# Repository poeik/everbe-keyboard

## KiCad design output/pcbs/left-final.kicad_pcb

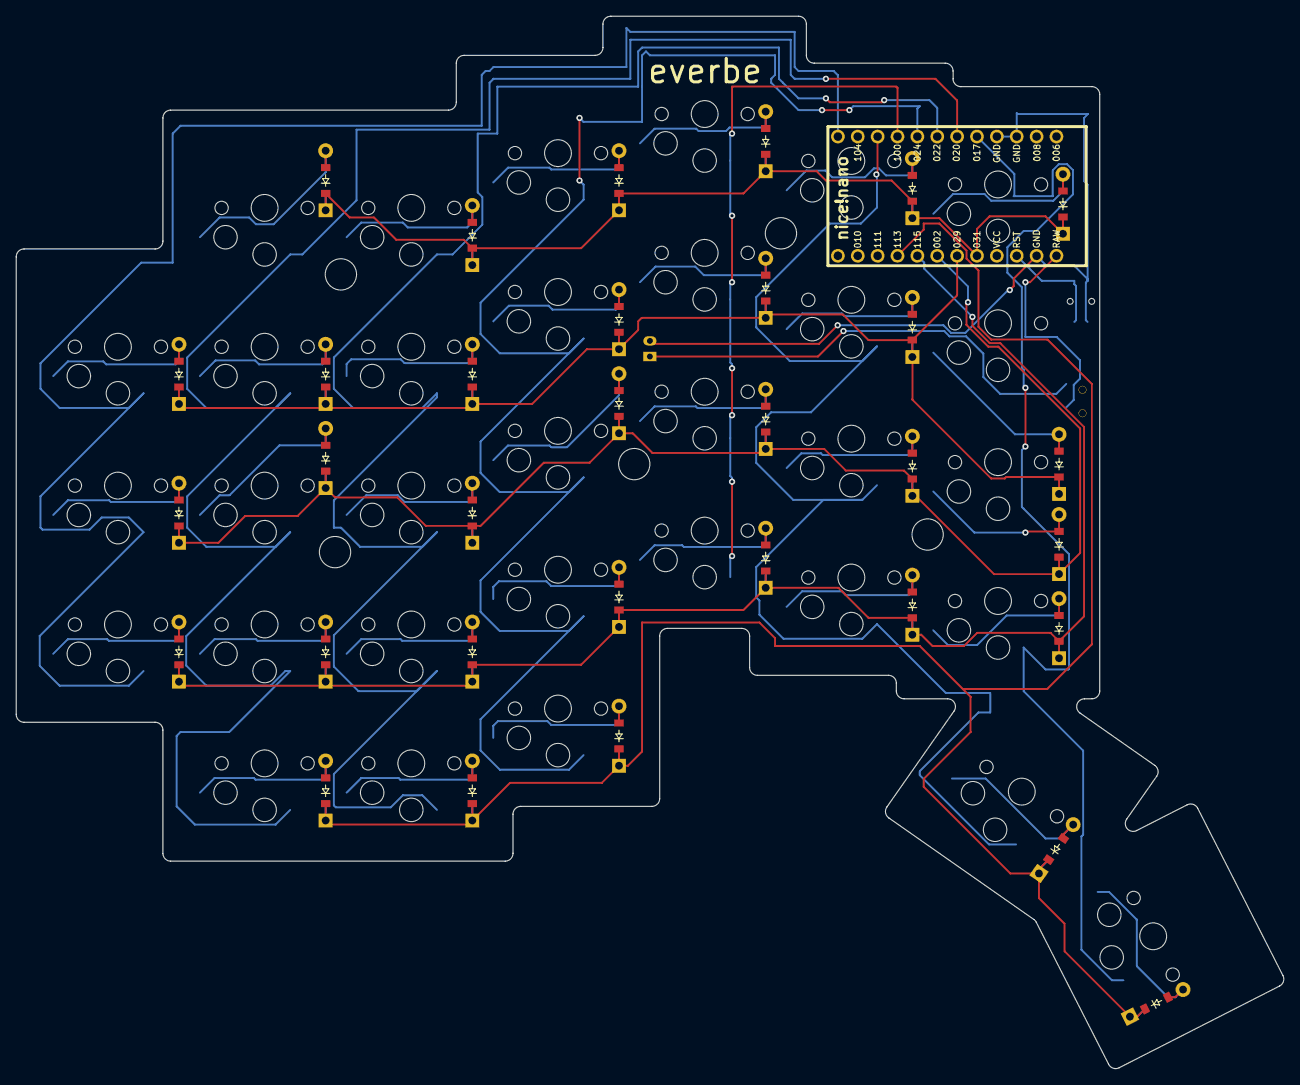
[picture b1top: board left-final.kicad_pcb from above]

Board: 2 copper layers, 162.0 x 134.5 mm, 68 parts (0 on the bottom side), 48 nets.

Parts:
B1: Panasonic_EVQPUL_EVQPUC
D1, D2, D3, D4, D5, D6, D7, D8, D9, D10, D11, D12, D13, D14, D15, D16, D17, D18, D19, D20, D21, D22, D23, D24, D25, D26, D27, D28, D29, D30, D31, D32: ComboDiode
JST1: JST_PH_S2B-PH-K_02x2.00mm_Angled
MCU1: nice_nano
S1, S2, S3, S4, S5, S6, S7, S8, S9, S10, S11, S12, S13, S14, S15, S16, S17, S18, S19, S20, S21, S22, S23, S24, S25, S26, S27, S28, S29, S30, S31, S32: PG1350
T1: SPDT_C128955

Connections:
GND: B1.1, JST1.2, MCU1.3, MCU1.4, MCU1.23
P002: D2.1, D9.1, D17.1, D20.1, D27.1, D29.1, D31.1, MCU1.18
P011: MCU1.10, S23.1, S24.1, S25.1, S26.1, S31.1
P017: MCU1.5, S27.1, S28.1, S29.1, S30.1, S32.1
P020: MCU1.6, S4.1, S5.1, S6.1, S7.1, S8.1
P022: MCU1.7, S9.1, S10.1, S11.1, S12.1, S13.1
P024: MCU1.8, S14.1, S15.1, S16.1, S17.1, S18.1
P029: D3.1, D6.1, D10.1, D14.1, D21.1, D26.1, D32.1, MCU1.19
P031: D11.1, D15.1, D18.1, D22.1, D28.1, D30.1, MCU1.20
P100: MCU1.9, S19.1, S20.1, S21.1, S22.1
P106: MCU1.12, S1.1, S2.1, S3.1
P113: D4.1, D7.1, D12.1, D24.1, D25.1, MCU1.16
P115: D1.1, D5.1, D8.1, D13.1, D16.1, D19.1, D23.1, MCU1.17
RAW: MCU1.24, T1.2
RST: B1.2, MCU1.22
far_default: D25.2, S32.2
fifth_bottom: D19.2, S23.2
fifth_home: D20.2, S24.2
fifth_num: D22.2, S26.2
fifth_top: D21.2, S25.2
first_bottom: D5.2, S5.2
first_home: D29.2, S6.2
first_mod: D4.2, S4.2
first_num: D30.2, S8.2
first_top: D6.2, S7.2
fourth_bottom: D16.2, S19.2
fourth_home: D17.2, S20.2
fourth_num: D18.2, S22.2
fourth_top: D32.2, S21.2
home_default: D24.2, S31.2
pos: JST1.1, T1.1
second_bottom: D8.2, S10.2
second_home: D9.2, S11.2
second_mod: D7.2, S9.2
second_num: D11.2, S13.2
second_top: D10.2, S12.2
sixth_bottom: D23.2, S27.2
sixth_home: D27.2, S28.2
sixth_num: D28.2, S30.2
sixth_top: D26.2, S29.2
third_bottom: D13.2, S15.2
third_home: D31.2, S16.2
third_mod: D12.2, S14.2
third_num: D15.2, S18.2
third_top: D14.2, S17.2
zeroth_bottom: D1.2, S1.2
zeroth_home: D2.2, S2.2
zeroth_top: D3.2, S3.2

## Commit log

2024-10-21 initial config (unrouted, without reset switch)
2024-10-21 add reset button
2024-10-21 finish left-pcb
2024-10-21 add reset button to config.yaml
2024-10-21 update gitignore
2024-10-22 remove unused pins from nice nano
2024-10-30 correctly place controller on left keyboard
2024-10-30 move reset battery switch to better position
2024-10-30 prepare ergogen config for the mirroring and & right pcb
2024-10-30 add config for right keyboard
2024-10-30 add additional zeroth column
2024-11-04 move text on right half
2024-11-04 add wired pcbs
2024-11-04 rerun ergogen
2025-01-02 fix pcb bug
